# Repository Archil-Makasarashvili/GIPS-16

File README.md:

# GIPS-16
GIPS-16-1 Soviet  plasma display controller

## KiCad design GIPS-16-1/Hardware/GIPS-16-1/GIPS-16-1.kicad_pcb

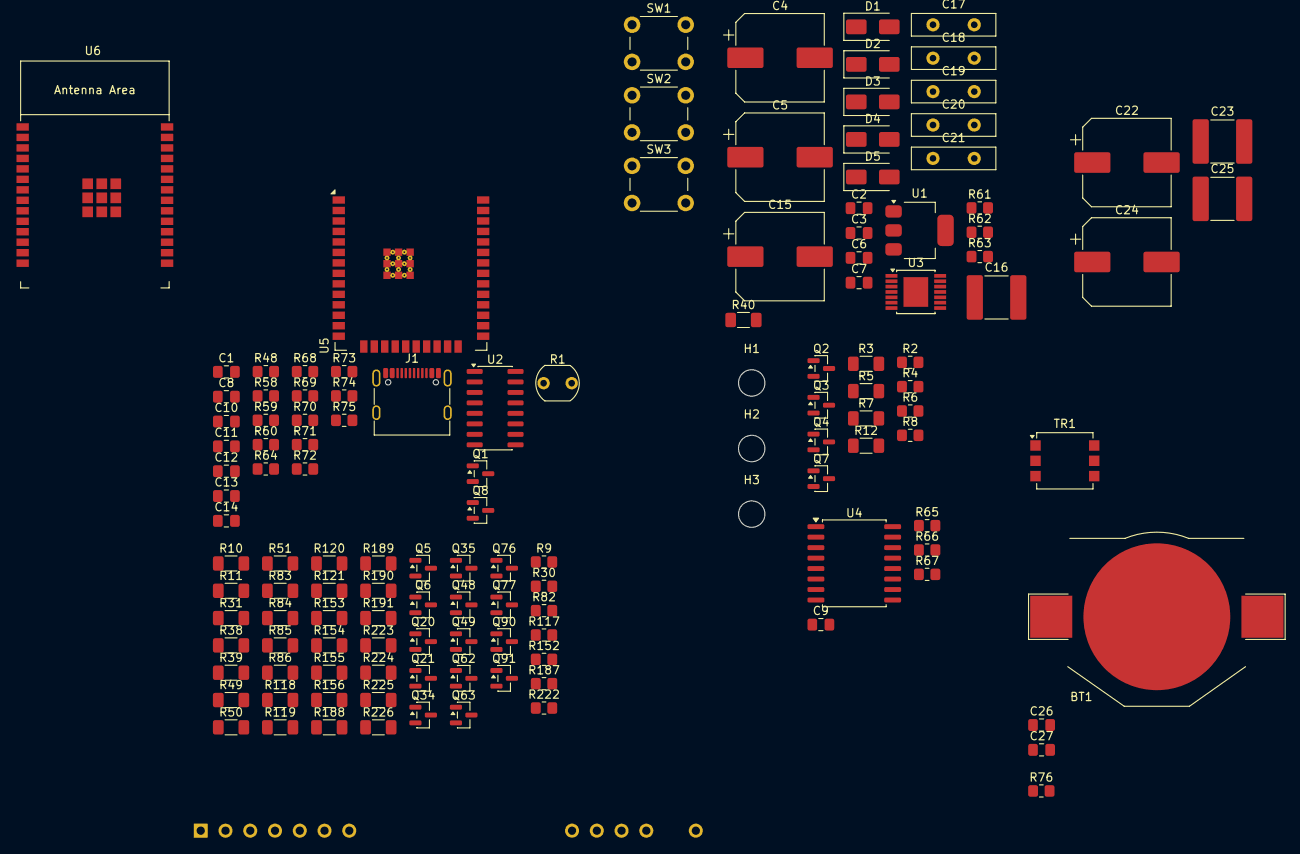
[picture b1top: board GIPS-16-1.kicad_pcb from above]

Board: 2 copper layers, 134 parts (1 on the bottom side), 92 nets, no tracks yet.

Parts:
BT1: Battery_Cell; BatteryHolder_Keystone_3002_1x2032
C1, C2, C3, C6, C7, C8, C9, C10, C11, C12, C13, C14, C26, C27: 0.1uF x 50V; C_0805_2012Metric_Pad1.18x1.45mm_HandSolder
C4, C5: 1000uF x 16v; CP_Elec_10x10.5
C15, C22, C24: 6.8uF x 470v; CP_Elec_10x10.5
C16, C23, C25: 1nF x 1KV; C_2220_5750Metric_Pad1.97x5.40mm_HandSolder
C17, C18, C19, C20, C21: 1nF x 1KV; C_Disc_D10.0mm_W2.5mm_P5.00mm
D1, D2, D3, D4, D5: US1M; D_SMA
H1, H2, H3: MountingHole; MountingHole_3.2mm_M3
J1: USB_C_Receptacle_USB2.0_16P; USB_C_Receptacle_G-Switch_GT-USB-7010ASV
J2: GIPS-16 Pins; GIPS-16-1_CON
M1: GIPS-16 3D Model; GIPS-16-1_3D
Q1, Q2, Q3, Q4, Q5, Q7, Q8, Q20, Q34, Q48, Q62, Q76, Q90: MMBTA42; SOT-23
Q6, Q21, Q35, Q49, Q63, Q77, Q91: MMBTA92; SOT-23
R1: R_Photo; R_LDR_5.1x4.3mm_P3.4mm_Vertical
R2, R4, R6, R8, R9, R30, R82, R117, R152, R187, R222: 1K; R_0805_2012Metric_Pad1.20x1.40mm_HandSolder
R3, R5, R7, R12: 220K; R_1206_3216Metric_Pad1.30x1.75mm_HandSolder
R10, R38, R83, R118, R153, R188, R223: 33K; R_1206_3216Metric_Pad1.30x1.75mm_HandSolder
R11, R49, R84, R119, R154, R189, R224: 430K; R_1206_3216Metric_Pad1.30x1.75mm_HandSolder
R31, R50, R85, R120, R155, R190, R225: 62K; R_1206_3216Metric_Pad1.30x1.75mm_HandSolder
R39, R51, R86, R121, R156, R191, R226: 47K; R_1206_3216Metric_Pad1.30x1.75mm_HandSolder
R40: 10M; R_1206_3216Metric_Pad1.30x1.75mm_HandSolder
R48, R60: 22R; R_0805_2012Metric_Pad1.20x1.40mm_HandSolder
R58, R59: 5.1K; R_0805_2012Metric_Pad1.20x1.40mm_HandSolder
R61: 2K; R_0805_2012Metric_Pad1.20x1.40mm_HandSolder
R62: 470K; R_0805_2012Metric_Pad1.20x1.40mm_HandSolder
R63: 75K; R_0805_2012Metric_Pad1.20x1.40mm_HandSolder
R64, R65, R66, R67, R68, R69, R70, R71, R72, R73, R74, R75, R76: 10K; R_0805_2012Metric_Pad1.20x1.40mm_HandSolder
SW1: Menu; SW_PUSH_6mm_H5mm
SW2: Set; SW_PUSH_6mm_H5mm
SW3: Mode; SW_PUSH_6mm_H5mm
TR1: CEEH54; Pulse_P0926NL
U1: AMS1117-3.3; SOT-223-3_TabPin2
U2: CH340C; SOIC-16_3.9x9.9mm_P1.27mm
U3: TPS55340; TSSOP-14-1EP_4.4x5mm_P0.65mm
U4: DS3231M; SOIC-16W_7.5x10.3mm_P1.27mm
U5: ESP32-WROOM-32E
U6: ESP32-C5-WROOM-1

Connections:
+3.3V: C3.1, C4.1, C8.1, C13.1, C14.1, C26.1, R1.1, R64.2, R65.2, R66.2, R67.2, R68.2, R69.2, R71.2, R72.2, R73.2, U1.2 (VO), U2.4 (V3), U2.16 (VCC), U4.2 (VCC), U5.2 (VDD)
+5V: C2.1, C5.1, J1.A4 (VBUS), J1.A9 (VBUS), J1.B4 (VBUS), J1.B9 (VBUS), TR1.1, U1.3 (VI), U3.3 (VIN), U3.4 (EN)
+120V: C15.1, C16.1, C20.1, D1.1 (K), D4.2 (A), R3.1, R5.1, R7.1, R12.1, R39.2, R51.2, R86.2, R121.2, R156.2, R191.2, R226.2
+240V: C18.1, C22.1, C23.1, D3.1 (K), Q6.2 (E), Q21.2 (E), Q35.2 (E), Q49.2 (E), Q63.2 (E), Q77.2 (E), Q91.2 (E), R10.1, R38.1, R83.1, R118.1, R153.1, R188.1, R223.1
+360V: C21.1, C24.1, C25.1, D5.1 (K), J2.21 (Uscan)
/Anode_Driver_1/Anode_In_1: R9.1, U5.26 (IO4)
/Anode_Driver_1/Anode_In_2: R30.1, U5.16 (IO13)
/Anode_Driver_1/Anode_In_3: R82.1, U5.27 (IO16)
/Anode_Driver_1/Anode_In_4: R117.1, U5.28 (IO17)
/Anode_Driver_1/Anode_In_5: R152.1, U5.30 (IO18)
/Anode_Driver_1/Anode_In_6: R187.1, U5.31 (IO19)
/Anode_Driver_1/Anode_In_7: R222.1, U5.37 (IO23)
/Anode_Driver_1/Anode_Out_1: J2.7 (A1), R31.2, R39.1
/Anode_Driver_1/Anode_Out_2: J2.5 (A2), R50.2, R51.1
/Anode_Driver_1/Anode_Out_3: J2.3 (A3), R85.2, R86.1
/Anode_Driver_1/Anode_Out_4: J2.1 (A4), R120.2, R121.1
/Anode_Driver_1/Anode_Out_5: J2.2 (A5), R155.2, R156.1
/Anode_Driver_1/Anode_Out_6: J2.4 (A6), R190.2, R191.1
/Anode_Driver_1/Anode_Out_7: J2.6 (A7), R225.2, R226.1
/Cathode_Driver/Cathode_In_0: R2.1, U5.10 (IO25)
/Cathode_Driver/Cathode_In_1: R4.1, U5.11 (IO26)
/Cathode_Driver/Cathode_In_2: R6.1, U5.12 (IO27)
/Cathode_Driver/Cathode_In_3: R8.1, U5.8 (IO32)
/Cathode_Driver/Cathode_Out_0: J2.16 (C0), Q2.3 (C), R3.2
/Cathode_Driver/Cathode_Out_1: J2.19 (C1), Q3.3 (C), R5.2
/Cathode_Driver/Cathode_Out_2: J2.18 (C2), Q4.3 (C), R7.2
/Cathode_Driver/Cathode_Out_3: J2.17 (C3), Q7.3 (C), R12.2
/MCU/Button_Menu: C10.1, R71.1, SW1.2, U5.6 (IO34)
/MCU/Button_Mode: C12.1, R73.1, SW3.2, U5.9 (IO33)
/MCU/Button_Set: C11.1, R72.1, SW2.2, U5.7 (IO35)
/MCU/EN: C1.1, Q1.3 (C), R64.1, U5.3 (EN)
/MCU/IO0: Q8.3 (C), R68.1, U5.25 (IO0)
/MCU/RX: U2.2 (TXD), U5.34 (RXD0/IO3)
/MCU/TX: U2.3 (RXD), U5.35 (TXD0/IO1)
/RTC/SCL: R66.1, U4.16 (SCL), U5.36 (IO22)
/RTC/SDA: R67.1, U4.15 (SDA), U5.33 (IO21)
GND: BT1.2 (-), C1.2, C2.2, C3.2, C4.2, C5.2, C6.2, C7.2, C8.2, C9.2, C10.2, C11.2, C12.2, C13.2, C14.2, C15.2, C16.2, C18.2, C20.2, C21.2, C22.2, C23.2, C24.2, C25.2, C26.2, C27.2, D2.2 (A), J1.A1 (GND), J1.A12 (GND), J1.B1 (GND), J1.B12 (GND), J1.SH (SHIELD), Q2.2 (E), Q3.2 (E), Q4.2 (E), Q5.2 (E), Q7.2 (E), Q20.2 (E), Q34.2 (E), Q48.2 (E), Q62.2 (E), Q76.2 (E), Q90.2 (E), R58.2, R59.2, R62.1, R63.1, R70.1, R76.1, SW1.1, SW2.1, SW3.1, TR1.3, U1.1 (GND), U2.1 (GND), U3.6 (SYNC), U3.7 (AGND), U3.12 (PGND), U3.13 (PGND), U3.14 (PGND), U3.15 (EPAD), U4.5 (GND), U4.6 (GND), U4.7 (GND), U4.8 (GND), U4.9 (GND), U4.10 (GND), U4.11 (GND), U4.12 (GND), U4.13 (GND), U5.1 (GND), U5.15 (GND), U5.38 (GND), U5.39 (GND)
unnamed: BT1.1 (+), C27.1, U4.14 (VBAT)
unnamed: C6.1, R61.1
unnamed: C17.1, C19.1, D1.2 (A), TR1.4
unnamed: C17.2, D2.1 (K), D3.2 (A)
unnamed: C19.2, D4.1 (K), D5.2 (A)
unnamed: J1.A5 (CC1), R58.1
unnamed: J1.B5 (CC2), R59.1
unnamed: Q1.1 (B), R74.1
unnamed: Q1.2 (E), R75.2, U2.14 (~RTS)
unnamed: Q2.1 (B), R2.2
unnamed: Q3.1 (B), R4.2
unnamed: Q4.1 (B), R6.2
unnamed: Q5.1 (B), R9.2
unnamed: Q5.3 (C), R11.2
unnamed: Q6.1 (B), R10.2, R11.1
unnamed: Q6.3 (C), R31.1
unnamed: Q7.1 (B), R8.2
unnamed: Q8.1 (B), R75.1
unnamed: Q8.2 (E), R74.2, U2.13 (~DTR)
unnamed: Q20.1 (B), R30.2
unnamed: Q20.3 (C), R49.2
unnamed: Q21.1 (B), R38.2, R49.1
unnamed: Q21.3 (C), R50.1
unnamed: Q34.1 (B), R82.2
unnamed: Q34.3 (C), R84.2
unnamed: Q35.1 (B), R83.2, R84.1
unnamed: Q35.3 (C), R85.1
unnamed: Q48.1 (B), R117.2
unnamed: Q48.3 (C), R119.2
unnamed: Q49.1 (B), R118.2, R119.1
unnamed: Q49.3 (C), R120.1
unnamed: Q62.1 (B), R152.2
unnamed: Q62.3 (C), R154.2
unnamed: Q63.1 (B), R153.2, R154.1
unnamed: Q63.3 (C), R155.1
unnamed: Q76.1 (B), R187.2
unnamed: Q76.3 (C), R189.2
unnamed: Q77.1 (B), R188.2, R189.1
unnamed: Q77.3 (C), R190.1
unnamed: Q90.1 (B), R222.2
unnamed: Q90.3 (C), R224.2
unnamed: Q91.1 (B), R223.2, R224.1
unnamed: Q91.3 (C), R225.1
unnamed: R40.2, R63.2
unnamed: TR1.2, U3.1 (SW), U3.2 (SW)
unnamed: J1.A6 (D+), J1.B6 (D+), R48.2, U2.5 (UD+)
unnamed: J1.A7 (D-), J1.B7 (D-), R60.2, U2.6 (UD-)
unnamed: R61.2, U3.8 (COMP)
unnamed: R62.2, U3.10 (FREQ)
unnamed: C7.1, U3.5 (SS)
unnamed: C9.1, R65.1
unnamed: R76.2, U5.24 (IO2)
unnamed: R69.1, U5.29 (IO5)
unnamed: R1.2, R70.2, U5.4 (SENSOR_VP)
unnamed: U6.1 (GND), U6.28 (GND), U6.29 (GND)

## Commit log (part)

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2026-06-10 Add files via upload
    Initial commit.
2026-06-10 Updated directory structure.
